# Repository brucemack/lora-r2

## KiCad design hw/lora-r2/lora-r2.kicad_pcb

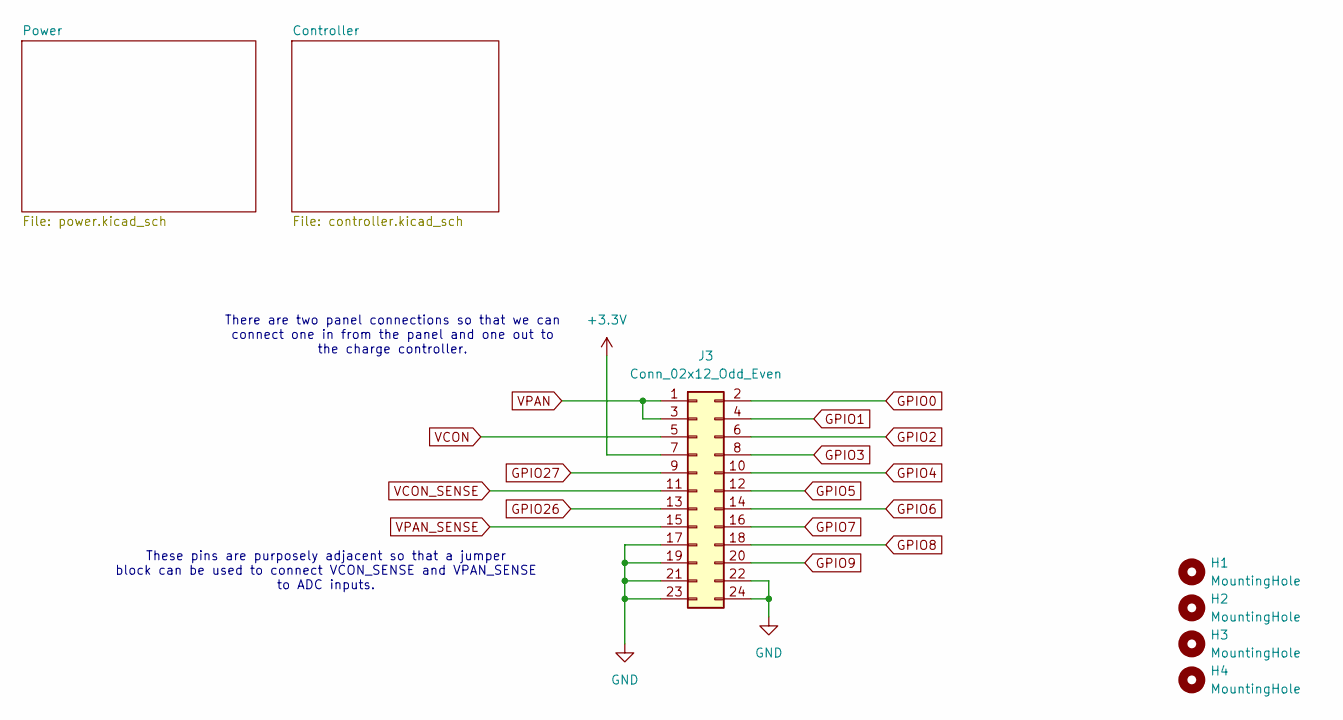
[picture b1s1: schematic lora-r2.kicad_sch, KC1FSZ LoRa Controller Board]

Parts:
H1, H2, H3, H4: MountingHole; MountingHole_3.5mm
J3: Conn_02x12_Odd_Even; PinHeader_2x12_P2.54mm_Vertical

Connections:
+3.3V: J3.7; also elsewhere on the board
GND: J3.17, J3.19, J3.21, J3.22, J3.23, J3.24; also elsewhere on the board
GPIO0: J3.2; also elsewhere on the board
GPIO1: J3.4; also elsewhere on the board
GPIO2: J3.6; also elsewhere on the board
GPIO3: J3.8; also elsewhere on the board
GPIO4: J3.10; also elsewhere on the board
GPIO5: J3.12; also elsewhere on the board
GPIO6: J3.14; also elsewhere on the board
GPIO7: J3.16; also elsewhere on the board
GPIO8: J3.18; also elsewhere on the board
GPIO9: J3.20; also elsewhere on the board
GPIO26: J3.13; also elsewhere on the board
GPIO27: J3.9; also elsewhere on the board
VCON: J3.5; also elsewhere on the board
VCON_SENSE: J3.11; also elsewhere on the board
VPAN: J3.1, J3.3; also elsewhere on the board
VPAN_SENSE: J3.15; also elsewhere on the board

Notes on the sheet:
These pins are purposely adjacent so that a jumper block can be used to connect VCON_SENSE and VPAN_SENSE to ADC inputs.
There are two panel connections so that we can connect one in from the panel and one out to the charge controller.

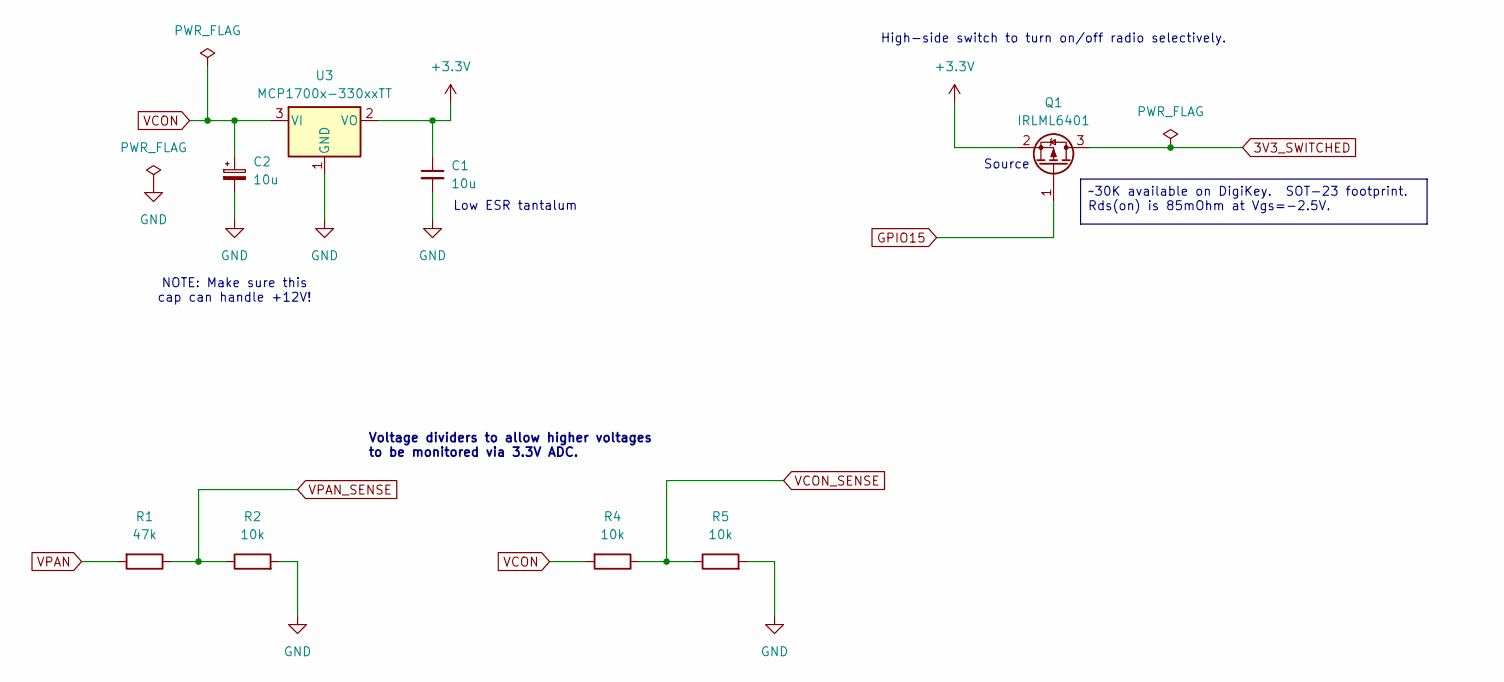
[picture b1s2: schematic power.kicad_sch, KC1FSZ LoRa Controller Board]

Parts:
C1: 10u; C_0805_2012Metric_Pad1.18x1.45mm_HandSolder
C2: 10u; CP_Elec_4x5.4
Q1: IRLML6401; SOT-23
R1: 47k; R_0805_2012Metric_Pad1.20x1.40mm_HandSolder
R2, R4, R5: 10k; R_0805_2012Metric_Pad1.20x1.40mm_HandSolder
U3: MCP1700x-330xxTT; SOT-23

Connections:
3V3_SWITCHED: Q1.3 (D); also elsewhere on the board
+3.3V: C1.1, Q1.2 (S), U3.2 (VO); also elsewhere on the board
GND: C1.2, C2.2, R2.2, R5.2, U3.1 (GND); also elsewhere on the board
GPIO15: Q1.1 (G); also elsewhere on the board
VCON: C2.1, R4.2, U3.3 (VI); also elsewhere on the board
VCON_SENSE: R4.1, R5.1; also elsewhere on the board
VPAN: R1.2; also elsewhere on the board
VPAN_SENSE: R1.1, R2.1; also elsewhere on the board

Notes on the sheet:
NOTE: Make sure this cap can handle +12V!
High-side switch to turn on/off radio selectively.
Source
Low ESR tantalum
Voltage dividers to allow higher voltages to be monitored via 3.3V ADC.
~30K available on DigiKey. SOT-23 footprint. Rds(on) is 85mOhm at Vgs=-2.5V.

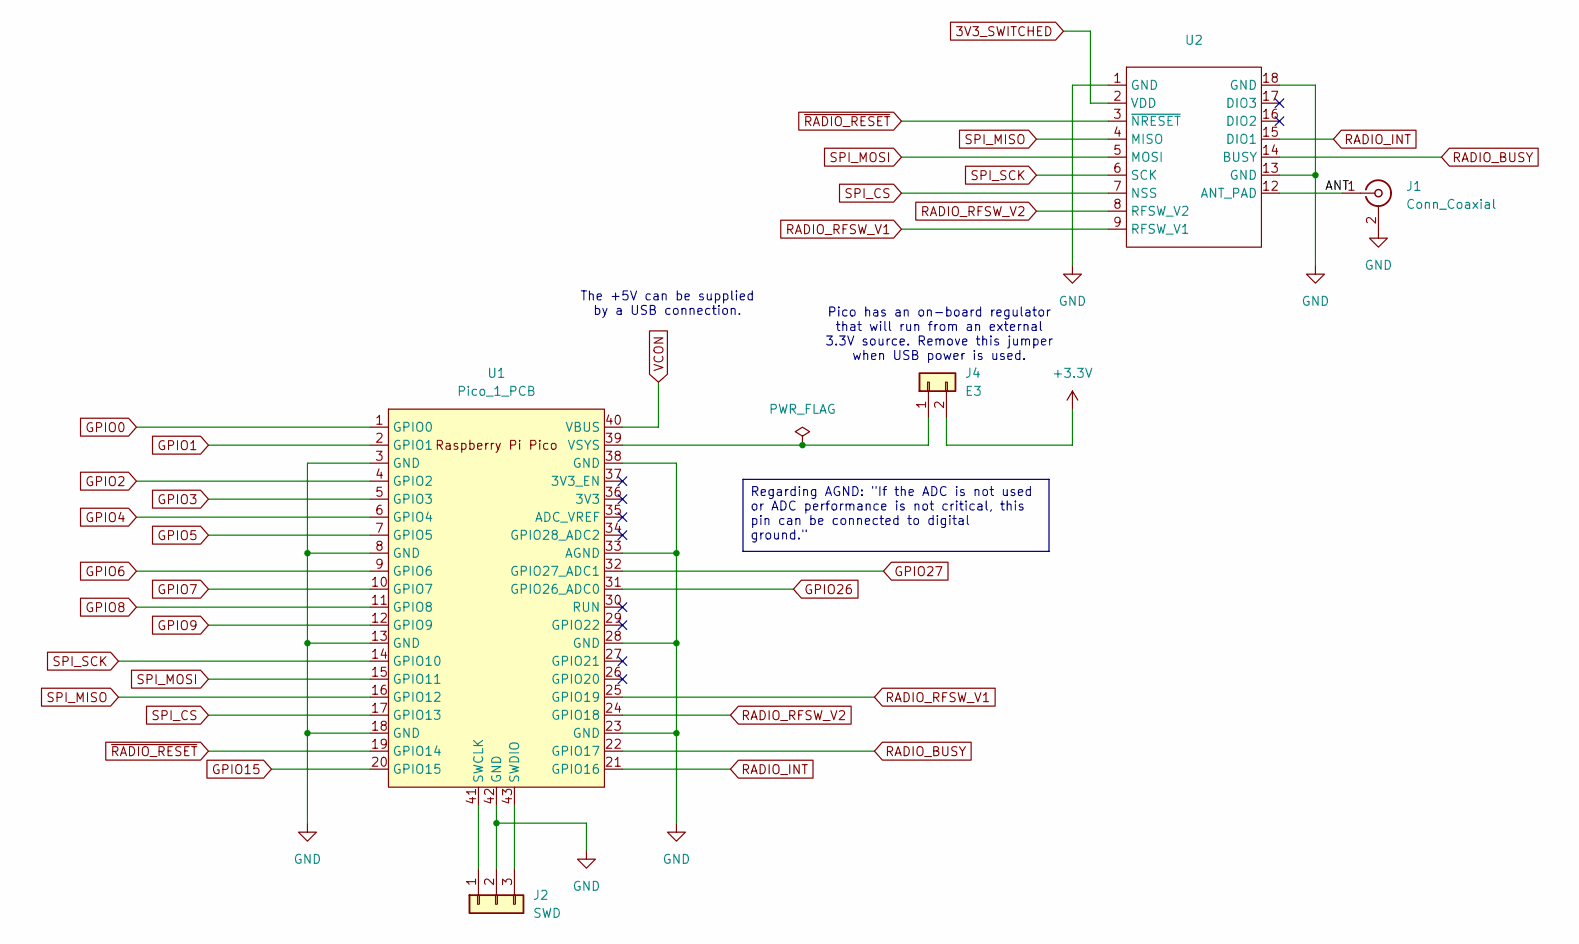
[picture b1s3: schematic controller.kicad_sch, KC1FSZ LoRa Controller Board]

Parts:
J1: Conn_Coaxial; SMA_Amphenol_132134_Vertical
J2: SWD; PinHeader_1x03_P2.54mm_Vertical
J4: E3; PinHeader_1x02_P2.54mm_Vertical
U1: Pico_1_PCB; RPi_Pico_SMD
U2: RYLR689-LoRa-Module

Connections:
3V3_SWITCHED: U2.2 (VDD); also elsewhere on the board
+3.3V: J4.2; also elsewhere on the board
/Controller/ANT: J1.1 (In), U2.12 (ANT_PAD)
GND: J1.2 (Ext), J2.2, U1.3 (GND), U1.8 (GND), U1.13 (GND), U1.18 (GND), U1.23 (GND), U1.28 (GND), U1.33 (AGND), U1.38 (GND), U1.42 (GND), U2.1 (GND), U2.13 (GND), U2.18 (GND); also elsewhere on the board
GPIO0: U1.1 (GPIO0); also elsewhere on the board
GPIO1: U1.2 (GPIO1); also elsewhere on the board
GPIO2: U1.4 (GPIO2); also elsewhere on the board
GPIO3: U1.5 (GPIO3); also elsewhere on the board
GPIO4: U1.6 (GPIO4); also elsewhere on the board
GPIO5: U1.7 (GPIO5); also elsewhere on the board
GPIO6: U1.9 (GPIO6); also elsewhere on the board
GPIO7: U1.10 (GPIO7); also elsewhere on the board
GPIO8: U1.11 (GPIO8); also elsewhere on the board
GPIO9: U1.12 (GPIO9); also elsewhere on the board
GPIO15: U1.20 (GPIO15); also elsewhere on the board
GPIO26: U1.31 (GPIO26_ADC0); also elsewhere on the board
GPIO27: U1.32 (GPIO27_ADC1); also elsewhere on the board
unnamed: J2.1, U1.41 (SWCLK)
unnamed: J2.3, U1.43 (SWDIO)
unnamed: J4.1, U1.39 (VSYS)
RADIO_BUSY: U1.22 (GPIO17), U2.14 (BUSY)
RADIO_INT: U1.21 (GPIO16), U2.15 (DIO1)
RADIO_RFSW_V1: U1.25 (GPIO19), U2.9 (RFSW_V1)
RADIO_RFSW_V2: U1.24 (GPIO18), U2.8 (RFSW_V2)
SPI_CS: U1.17 (GPIO13), U2.7 (NSS)
SPI_MISO: U1.16 (GPIO12), U2.4 (MISO)
SPI_MOSI: U1.15 (GPIO11), U2.5 (MOSI)
SPI_SCK: U1.14 (GPIO10), U2.6 (SCK)
VCON: U1.40 (VBUS); also elsewhere on the board
~RADIO_RESET: U1.19 (GPIO14), U2.3 (~NRESET)

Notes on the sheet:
The +5V can be supplied by a USB connection.
Pico has an on-board regulator that will run from an external 3.3V source. Remove this jumper when USB power is used.
Regarding AGND: "If the ADC is not used or ADC performance is not critical, this pin can be connected to digital ground."

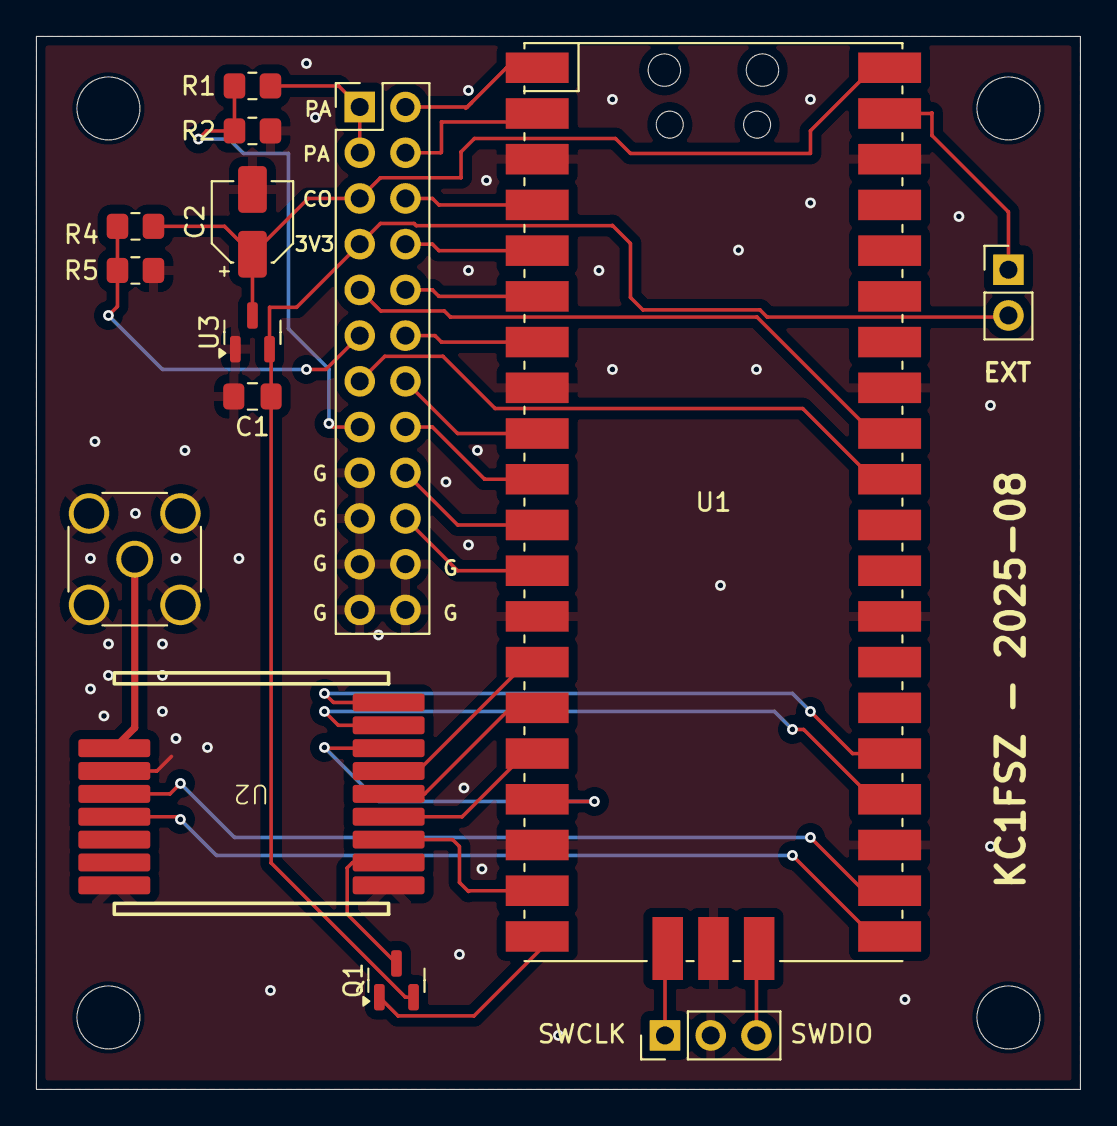
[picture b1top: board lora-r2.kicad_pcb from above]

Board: 2 copper layers, 58.0 x 58.5 mm, 18 parts (0 on the bottom side), 33 nets.

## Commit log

2025-05-07 Initial layout on LoRa R2
2025-05-07 DRC passing
2025-05-08 Working on PCB
2025-05-08 Making progress on layout
2025-05-08 First layout that passes DRC
2025-05-08 Generated first Gerbers
2025-05-08 Ready for fabrication
2025-05-08 SENT TO FAB (2025-05-08 13:04)
2025-05-11 Revision (before fab) - can power radio from USB now
2025-05-12 Ready to sent to fab

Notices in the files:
hw/lora-r2/controller.kicad_sch:
Copyright (C) 2025, Bruce MacKinnon
